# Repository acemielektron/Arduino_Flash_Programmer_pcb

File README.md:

# Arduino_Flash_Programmer_pcb
diy single sided pcb for serprog based flash programmer for flashrom.

On this pcb arduino pro mini is powered with 3.3v and used with a 3.3v usb serial adapter such as https://github.com/acemielektron/FT230X_usb_serial_PCB otherwise 3.3v parts might fry.

Serprog home page: https://www.flashrom.org/Serprog/Arduino_flasher

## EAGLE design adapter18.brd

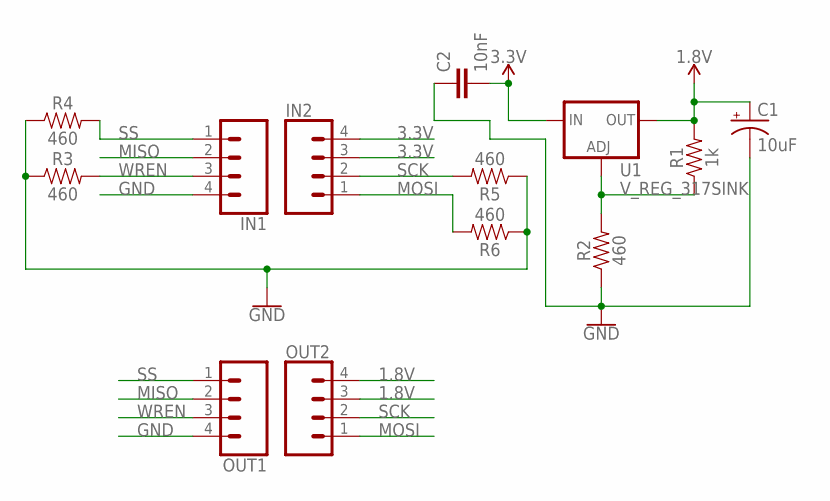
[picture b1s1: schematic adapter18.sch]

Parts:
C1: 10uF; CPOL-RADIAL-2.5MM-5MM
C2: 10nF; CAP-PTH-10MM
IN1, IN2: CONN_04; 1X04
OUT1, OUT2: CONN_04; 1X04
R1: 1k; AXIAL-0.3
R2, R3, R4, R5, R6: 460; AXIAL-0.3
U1: V_REG_317SINK; TO220-ADJ

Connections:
1.8V: C1.1 (+), OUT2.3, OUT2.4, R1.P$2 (2), U1.OUT
3.3V: C2.2, IN2.3, IN2.4, U1.IN
GND: C1.2 (-), C2.1, IN1.4, OUT1.4, R2.P$1 (1), R3.P$1 (1), R4.P$1 (1), R5.P$1 (1), R6.P$1 (1)
MISO: IN1.2, OUT1.2
MOSI: IN2.1, OUT2.1, R6.P$2 (2)
unnamed: R1.P$1 (1), R2.P$2 (2), U1.ADJ
SCK: IN2.2, OUT2.2, R5.P$2 (2)
SS: IN1.1, OUT1.1, R4.P$2 (2)
WREN: IN1.3, OUT1.3, R3.P$2 (2)

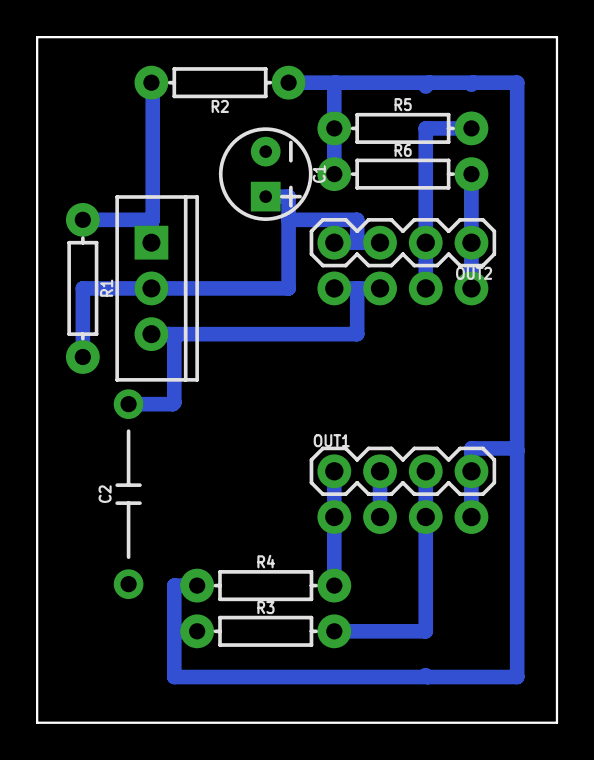
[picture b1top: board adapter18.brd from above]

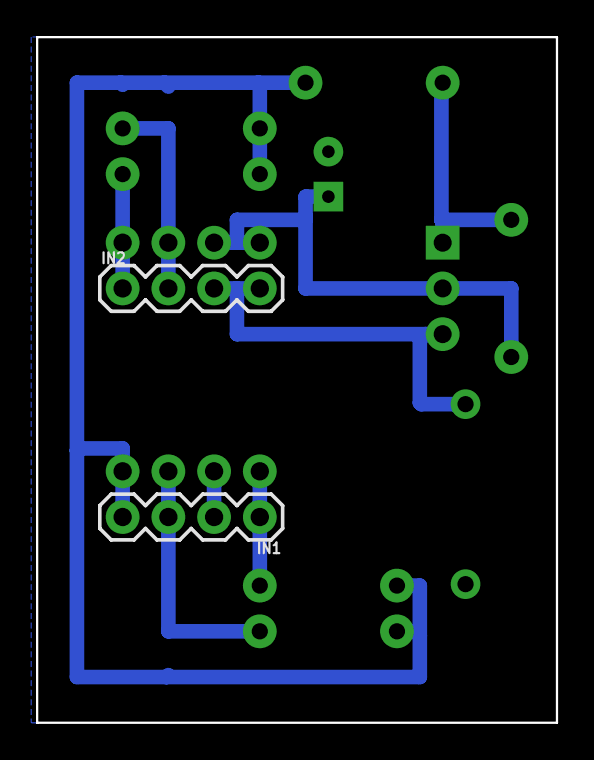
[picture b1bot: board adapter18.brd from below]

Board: 2 copper layers, 28.9 x 38.1 mm, 13 parts (2 on the bottom side), 9 nets.

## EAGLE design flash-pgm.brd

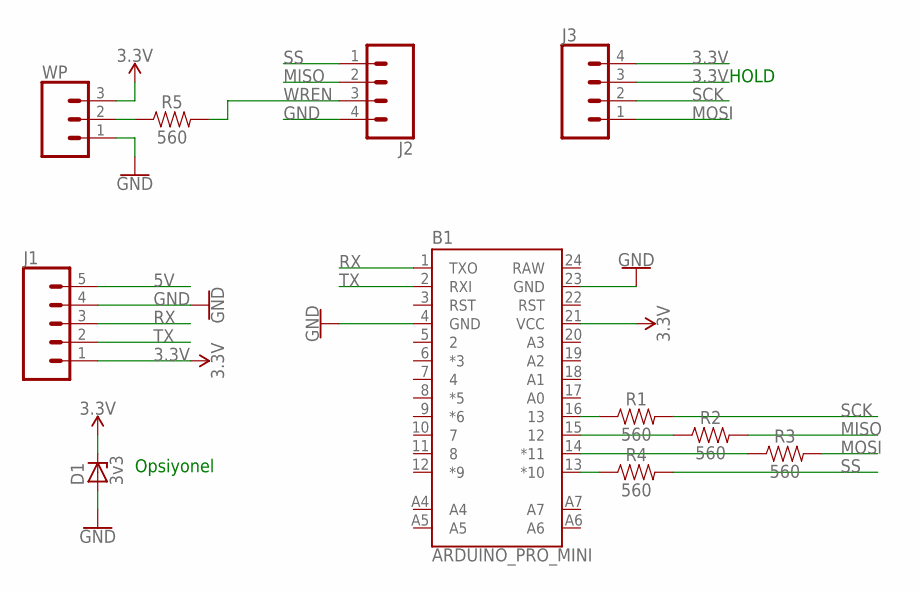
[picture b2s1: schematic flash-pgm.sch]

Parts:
B1: ARDUINO_PRO_MINI
D1: 3v3; C1702-15
J1: CONN_05; 1X05
J2, J3: CONN_04; 1X04
R1, R2, R3, R4, R5: 560; AXIAL-0.3
WP: CONN_03; 1X03

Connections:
3.3V: B1.21 (VCC), D1.C, J1.1, J3.3, J3.4, WP.3
5V: J1.5
GND: B1.4 (GND), B1.23 (GND), D1.A, J1.4, J2.4, WP.1
MISO: J2.2, R2.P$2 (2)
MOSI: J3.1, R3.P$2 (2)
unnamed: B1.16 (13), R1.P$1 (1)
unnamed: R5.P$1 (1), WP.2
unnamed: B1.15 (12), R2.P$1 (1)
unnamed: B1.14 (*11), R3.P$1 (1)
unnamed: B1.13 (*10), R4.P$1 (1)
RAW: B1.24 (RAW)
RX: B1.1 (TXO), J1.3
SCK: J3.2, R1.P$2 (2)
SS: J2.1, R4.P$2 (2)
TX: B1.2 (RXI), J1.2
WREN: J2.3, R5.P$2 (2)

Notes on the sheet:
HOLD
Opsiyonel

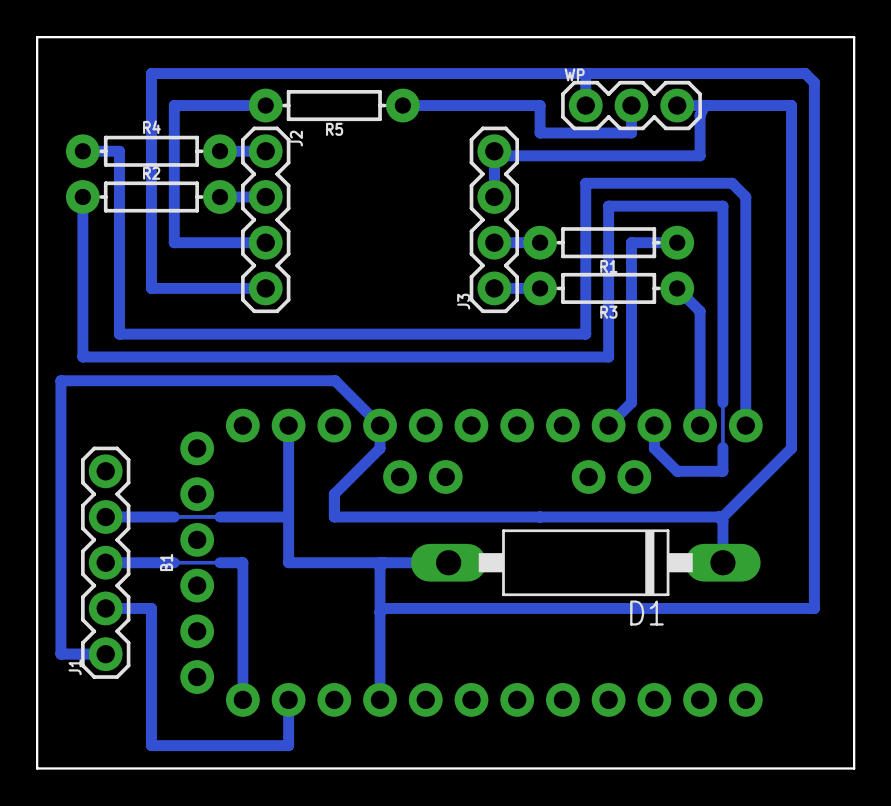
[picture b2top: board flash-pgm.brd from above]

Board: 2 copper layers, 45.4 x 40.6 mm, 11 parts (0 on the bottom side), 14 nets.

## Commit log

2019-02-14 1.8v adapter

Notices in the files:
parts and their libraries:
SparkFun-Connectors: Licensing: Creative Commons ShareAlike 4.0 International - https://creativecommons.org/licenses/by-sa/4.0
